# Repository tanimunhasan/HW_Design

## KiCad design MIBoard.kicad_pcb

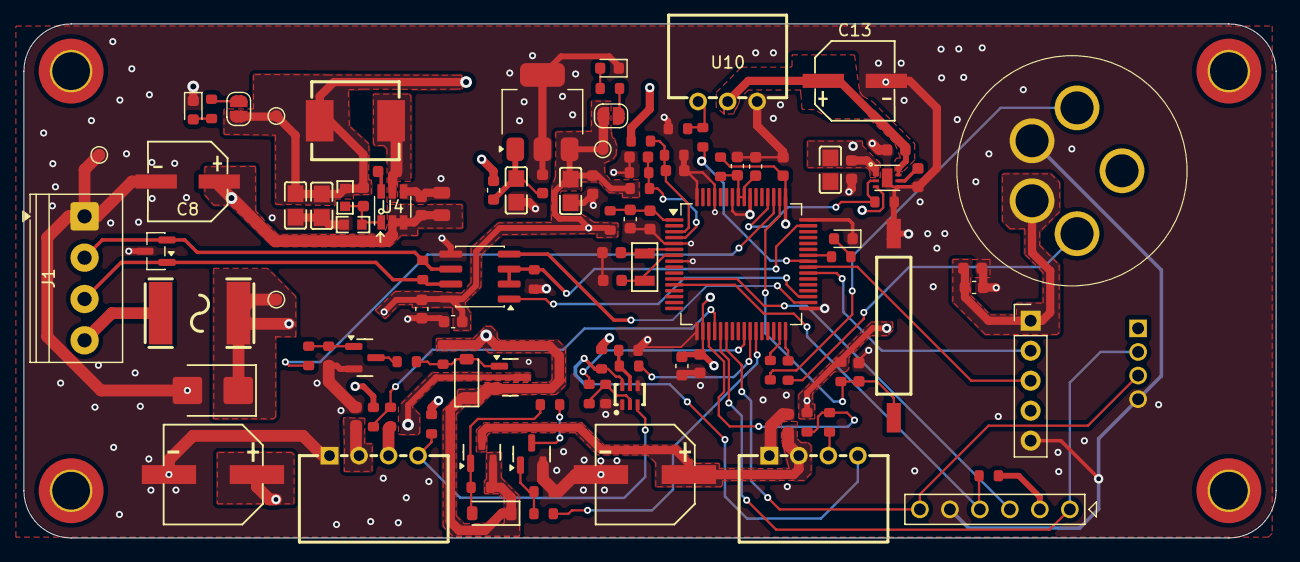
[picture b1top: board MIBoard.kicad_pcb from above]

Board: 4 copper layers, 106.1 x 43.5 mm, 114 parts (1 on the bottom side), 62 nets.

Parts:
C1: 10uF; C_0603_1608Metric
C2, C3: 100nF 16V; C_0603
C4, C5, C10, C24, C27, C30, C31, C35, C39, C40, C41, C42: 100nF; C_0603
C6, C33: 1.0uF; C_0603_1608Metric
C7: 22uF_0603_16V; C_0603_1608Metric
C8: 47uF 35V; CAP-SMD_BD6.3-L6.6-W6.6-LS7.6-RD
C9: 10uF; C_0805
C11, C12: 12pF; C_0603
C13: 470uF; CAP-SMD_BD6.3-L6.6-W6.6-LS7.3-FD-H7.7
C14, C15, C22: 22uF_0805_10V; C0805
C18, C25: 10nF; C_0603
C19, C26: 10uF 10V; C0805
C28, C29: 220uF 35V; CAP-SMD_BD8.0-L8.3-W8.3-LS9.3-FD
C32: 100nF_0603_16V; C_0603_1608Metric
C34: 4.7nF; C_0603
C37, C38: 1.0uF 16V; C_0603_1608Metric
CN1, CN2: 4 Pin Connector 2.5mm; CONN-TH_4P-P2.50_ZX-XH2.54-4PWZ
D1: SMBJ18A; D_SMB
D2: LED; LED_0603_1608Metric
D3: RED_LED; LED_0603_1608Metric
D4: BLUE_LED; LED_0603_1608Metric
D5, D6: BZT52C8V2; D_SOD-123
D7: SM712_SOT23; SOT-23
FB1: FerriteBead; L_0603_1608Metric
H1, H2, H3, H4: MountingHole; MountingHole_3.2mm_M3_ISO14580_Pad_TopOnly
J1: Screw_Terminal_01x04; TerminalBlock_Phoenix_PT-1,5-4-3.5-H_1x04_P3.50mm_Horizontal
J2: Conn_01x06_Pin; Program_Pin_MSP430
J3: Conn_01x05_Pin; PinHeader_1x05_P2.54mm_Vertical
JP1, JP2: SolderJumper_2_Open; SolderJumper-2_P1.3mm_Open_RoundedPad1.0x1.5mm
L1: 6.8uH 5A; IND-SMD_L7.4-W6.6_SRG0630
Q1, Q3: AO3401A; Q_SOT-23
Q2, Q4: 2N7002; Q_SOT-23
Q5: 2N7002DW; SOT-363-6_L2.0-W1.3-P0.65-LS2.1-BL
R1: 10Ω; R_0603
R2, R10, R14, R15, R18, R20, R21, R25, R28, R29, R38, R39: 100kΩ; R_0603
R3, R24, R30, R31, R32, R33: 10kΩ; R_0603
R4: 22Ω; R_0603
R5: 2.2kΩ; R_0603
R6: 158kΩ; R0603
R7: 30.1kΩ; R0603
R8, R9: 4.7kΩ; R_0603
R11, R13, R22, R23, R34, R35, R36: 1kΩ; R_0603
R12: 47kΩ; R_0603
R17, R19, R26, R27: 100Ω; R_0603
R37: 120Ω; R_0603
TP1, TP2, TP3, TP4: TestPoint; TestPoint_Pad_D1.0mm
U1: REED SWITCH; SENSOR-SMD_59170-1-S-00-D
U2: 5A 30V; F2920
U3: 4 Pin Connector 2mm; CONN-TH_4P-P2.00_S4B-PH-K-S-LF-SN
U4: AP63301WU-7; TSOT-23-6
U5: MSP430FR5043IPMR; LQFP-64_10x10mm_P0.5mm
U6: N2O Sensor; Adapter-N2O_onboard
U7: AP7361C-33E-13; SOT-223-3_TabPin2
U8: THVD1450D; SOIC-8_3.9x4.9mm_P1.27mm
U9: TPS22965DSGT; WSON-8_L2.0-W2.0-P0.50-TL-EP
U10: 3 Pin Connector 2.5mm; HDR-TH_3P-P2.50_ZX-XH2.54-3PWZ
X1: 32.768kHz; OSC-SMD_L3.2-W1.5

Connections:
+3V3: C2.1, C10.1, C22.1, C24.2, C32.1, C33.1, C38.1, J2.2, JP2.2 (B), R1.2, R2.1, R3.1, R4.1, R14.1, R30.1, R31.1, TP4.1 (1_1), U5.18 (DVCC1), U5.49 (DVCC3), U7.3 (VO), U8.8 (VCC)
+5V: C1.1, C14.1, C15.1, C26.2, C27.1, C41.2, C42.1, FB1.1, J3.1, JP1.2 (B), L1.2, R6.2, R10.1, R32.1, R33.1, TP3.1 (1_1), U6.4 (VCC), U9.1 (VIN), U9.2 (VIN), U9.4 (VBIAS)
+12V: C8.1, C9.1, C40.2, D1.1, D5.1, D6.1, Q1.2 (S), Q3.2 (S), R18.1, R39.1, TP1.1 (1_1), U2.2, U4.2 (EN), U4.3 (VIN)
/3V3_MON: C25.1, R14.2, R15.1, U5.4 (P1.1/UCA1STE/TA4.0/A1/C1/VREF+/VeREF+)
/5V_MON: C18.1, R10.2, R12.1, U5.3 (P1.0/UCA1CLK/TA1.0/A0/C0/VREF-/VeREF-)
/+12V_Fan1: C4.1, C29.1, CN2.2, Q3.3 (D)
/+12V_Fan2: C28.1, C30.1, CN1.2, Q1.3 (D)
/AVCC: C3.1, C37.1, R1.1, U5.1 (AVCC1)
/DBG_RX: J2.6, U3.3, U5.22 (P2.1/UCA1STE/UCA3SOMI/UCA3RXD)
/DBG_TX: J2.1, U3.2, U5.21 (P2.0/UCA1CLK/UCA3SIMO/UCA3TXD)
/FAN1_EN: R19.1, U5.27 (P3.1/TA1CLK/TB0.1/MTIF_OUT_IN)
/FAN1_PWM: R27.1, U5.25 (P1.4/TB0.4/UCB0STE/A2/C2)
/FAN1_PWM_Connector: CN2.4, Q5.6 (D1), R33.2
/FAN1_TACH: R31.2, R35.1, U5.19 (P1.2/UCA1SIMO/UCA1TXD/TA1.0/A8/C8)
/FAN2_EN: R17.1, U5.51 (P3.4/SMCLK/DMAE0)
/FAN2_PWM: R26.1, U5.26 (P1.5/TB0.5/UCB0CLK/A3/C3)
/FAN2_PWM_Connector: CN1.4, Q5.3 (D2), R32.2
/FAN2_TACH: R30.2, R34.1, U5.20 (P1.3/UCA1SOMI/UCA1RXD/TA1.1/A9/C9)
/GRN_LED: R5.1, U5.42 (P6.0/TA0CLK/COUT)
/LFXIN: C12.2, U5.6 (PJ.4/LFXIN), X1.2
/LFXOUT: C11.2, U5.7 (PJ.5/LFXOUT), X1.1
/PVCC: C6.1, C7.1, R4.2, U5.56 (PVCC), U5.57 (PVCC)
/RS485_A: D7.2 (A2), J1.2, R37.1, U8.6 (A)
/RS485_B: D7.1 (A1), J1.3, R37.2, U8.7 (B)
/RST_SBWTDIO_N: J2.4, R2.2, U5.12 (RST/NMI/SBWTDIO)
/SCL: J3.3, U5.40 (P5.6/TB0OUTH/UCB1SOMI/UCB1SCL)
/SDA: J3.2, U5.39 (P5.5/TA4.1/UCB1SIMO/UCB1SDA)
/SERVO VCC: C13.1, C35.1, U9.7 (VOUT), U9.8 (VOUT), U10.2
/SERVO_EN: R25.1, U5.52 (P3.5/ACLK/COUT), U9.3 (ON)
/SERVO_PWM: R36.1, U5.41 (P5.7/TA0.2/UCB1STE)
/SW: C39.1, L1.1, U4.5 (SW)
/TEST_SBWCLK: J2.3, U5.11 (TEST/SBWCLK)
DI/TXD: U5.34 (P5.0/TB0.0/UCA2SIMO/UCA2TXD), U8.4 (DI)
GND: C1.2, C2.2, C3.2, C4.2, C5.2, C6.2, C7.2, C8.2, C9.2, C10.2, C11.1, C12.1, C13.2, C14.2, C15.2, C18.2, C19.1, C22.2, C24.1, C25.2, C26.1, C27.2, C28.2, C29.2, C30.2, C31.1, C32.2, C33.2, C34.2, C35.2, C37.2, C38.2, C40.1, C41.1, CN1.1, CN2.1, D1.2, D2.1 (K), D3.1 (K), D4.1 (K), D7.3 (common), J1.1, J2.5, J3.5, Q2.2 (S), Q4.2 (S), Q5.1 (S1), Q5.4 (S2), R7.1, R12.2, R15.2, R20.2, R21.2, R24.2, R25.2, R28.2, R29.2, R38.2, TP2.1 (1_1), U1.2, U3.4, U4.4 (GND), U5.5 (AVSS2), U5.8 (AVSS3), U5.17 (DVSS1), U5.33 (DVSS2), U5.48 (DVSS3), U5.55 (PVSS2), U5.58 (PVSS), U5.61 (AVSS4), U5.64 (AVSS1), U6.5 (GND), U7.2 (GND), U8.5 (GND), U9.5 (GND), U9.9 (EP), U10.1
N2O_RXD: R13.2, U5.32 (P4.4/UCA0SOMI/UCA0RXD)
N2O_TXD: R11.1, U5.31 (P4.3/UCA0SIMO/UCA0TXD)
unnamed: CN1.3, R34.2
unnamed: CN2.3, R35.2
unnamed: D2.2 (A), R5.2
unnamed: D3.2 (A), R8.2
unnamed: D4.2 (A), R9.2
unnamed: J1.4, U2.1
unnamed: JP1.1 (A), R8.1
unnamed: JP2.1 (A), R9.1
unnamed: D5.2, Q1.1 (G), R22.1, R39.2
unnamed: Q2.3 (D), R22.2
unnamed: Q2.1 (G), R17.2, R20.1
unnamed: D6.2, Q3.1 (G), R18.2, R23.1
unnamed: Q4.3 (D), R23.2
unnamed: Q4.1 (G), R19.2, R21.1
unnamed: Q5.2 (G1), R27.2, R29.1
unnamed: Q5.5 (G2), R26.2, R28.1
unnamed: R36.2, R38.1, U10.3
unnamed: C39.2, U4.6 (BST)
unnamed: C42.2, R6.1, R7.2, U4.1 (FB)
unnamed: C5.1, R3.2, U1.1, U5.50 (P3.3/MCLK/TB0.3/XPB1)
unnamed: R11.2, U6.3 (RX)
unnamed: R13.1, U6.2 (TX)
unnamed: C19.2, C31.2, FB1.2, U7.1 (VI)
unnamed: C34.1, U9.6 (CT)
R0/RXD: U5.35 (P5.1/TB0.1/UCA2SOMI/UCA2RXD), U8.1 (RO)
RS485_DE/RE Ctrl: R24.1, U5.47 (P6.2/TB0CLK), U8.2 (~RE), U8.3 (DE)
